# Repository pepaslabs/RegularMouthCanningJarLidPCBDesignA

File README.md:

# RegularMouthCanningJarLidPCBDesignA

A PCB which acts as a lid for a regular mouth canning jar.

# Status

This is still an untested work-in-progress.

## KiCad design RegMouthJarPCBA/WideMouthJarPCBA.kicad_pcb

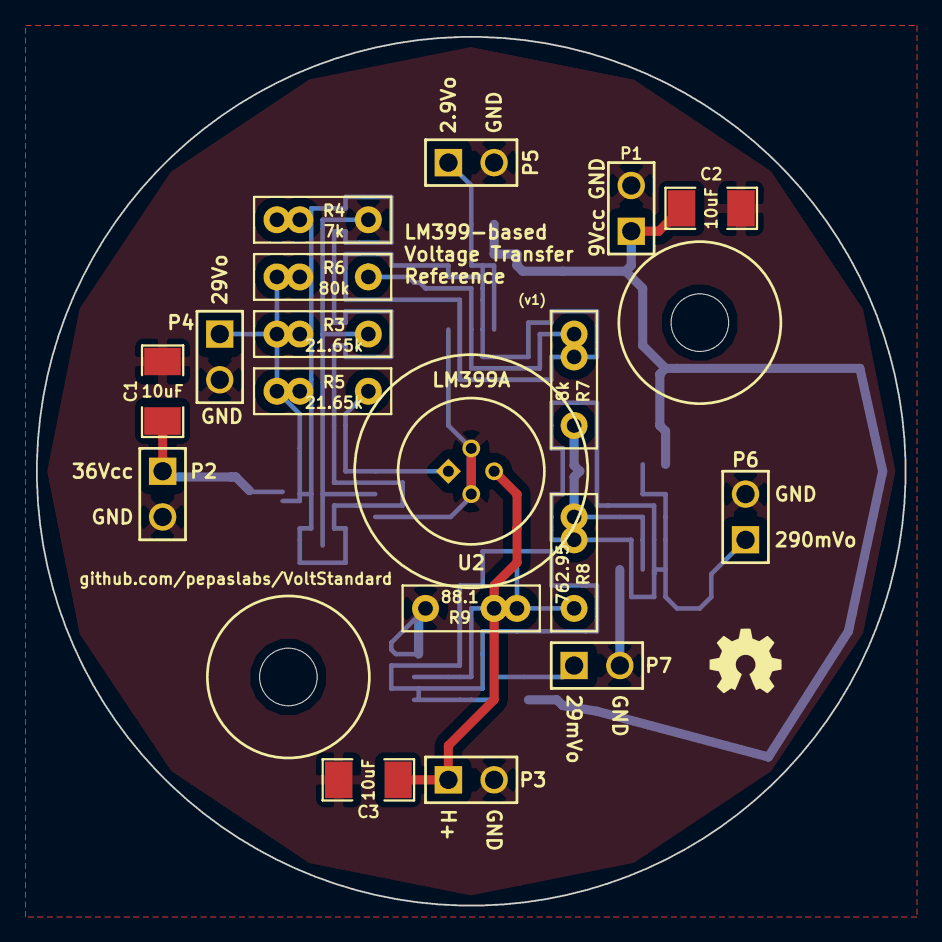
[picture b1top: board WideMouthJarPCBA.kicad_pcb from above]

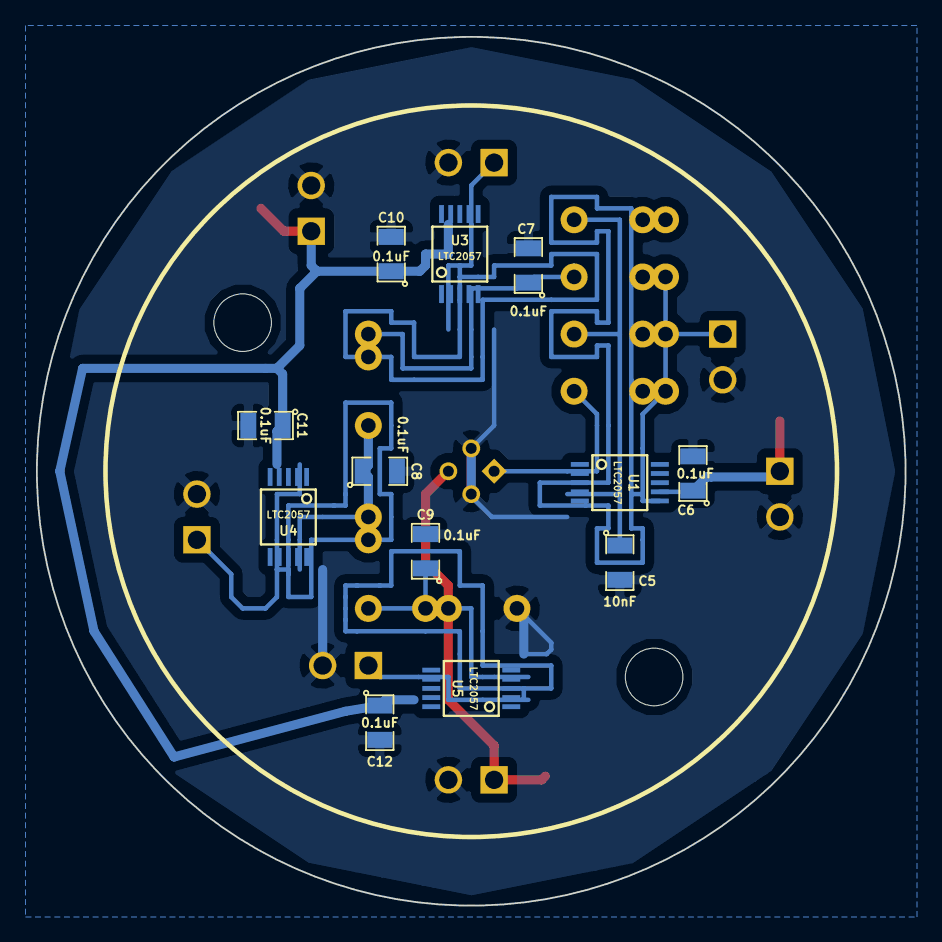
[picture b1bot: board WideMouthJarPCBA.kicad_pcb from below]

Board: 2 copper layers, 48.3 x 48.3 mm, 32 parts (12 on the bottom side), 13 nets.

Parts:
C1, C2, C3: 10uF; SM1206
C5: 10nF; SM0805
C6, C7, C8, C9, C10, C11, C12: 0.1uF; SM0805
H***: Val**; hole_M3
H***#2: Val**; hole_M3
P1, P2, P3, P4, P5, P6, P7: CONN_2; PIN_ARRAY_2X1
R3, R5: 21.65k; R_BOX
R4: 7k; R_BOX
R6: 80k; R_BOX
R7: 8k; R_BOX
R8: 762.95; R_BOX
R9: 88.1; R_BOX
U1, U3, U4, U5: LTC2057; MSOP10-0.5
U2: LM399A; TO-46-PLASTIC

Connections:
2.9Vo: P5.1, U3.2, U3.6
9V: C2.1, C10.1, C11.1, C12.1, P1.1, U3.7, U4.7, U5.7
29Vo: P4.1, R3.1, R5.1, R6.1, U1.6
29mVo: P7.1, U5.2, U5.6
36V: C1.1, C6.1, P2.1, U1.7
290mVo: P6.1, U4.2, U4.6
/2.9V: C7.1, R6.2, R7.1, U3.3
/29mV: C9.1, R8.2, R9.1, U5.3
/290mV: C8.1, R7.2, R8.1, U4.3
/Op-: C5.1, R3.2, R4.1, U1.3
/Vz: R5.2, U1.2, U2.1
GND: C1.2, C2.2, C3.2, C5.2, C6.2, C7.2, C8.2, C9.2, C10.2, C11.2, C12.2, P1.2, P2.2, P3.2, P4.2, P5.2, P6.2, P7.2, R4.2, R9.2, U1.4, U2.2, U2.4, U3.4, U4.4, U5.4
H+: C3.1, P3.1, U2.3

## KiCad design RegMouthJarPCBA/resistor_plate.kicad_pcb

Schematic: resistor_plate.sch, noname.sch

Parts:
H1, H2: HOLE
P1: CONN_4
R1, R2, R3, R4: R

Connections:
unnamed: R1.1, R4.1
unnamed: P1.3, P1.4, R2.2, R3.2, R4.2
unnamed: P1.1, P1.2, R1.2, R2.1, R3.1

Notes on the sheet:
Pinout: 1: Sense+ 2: Force+ 3: Force- 4: Sense-

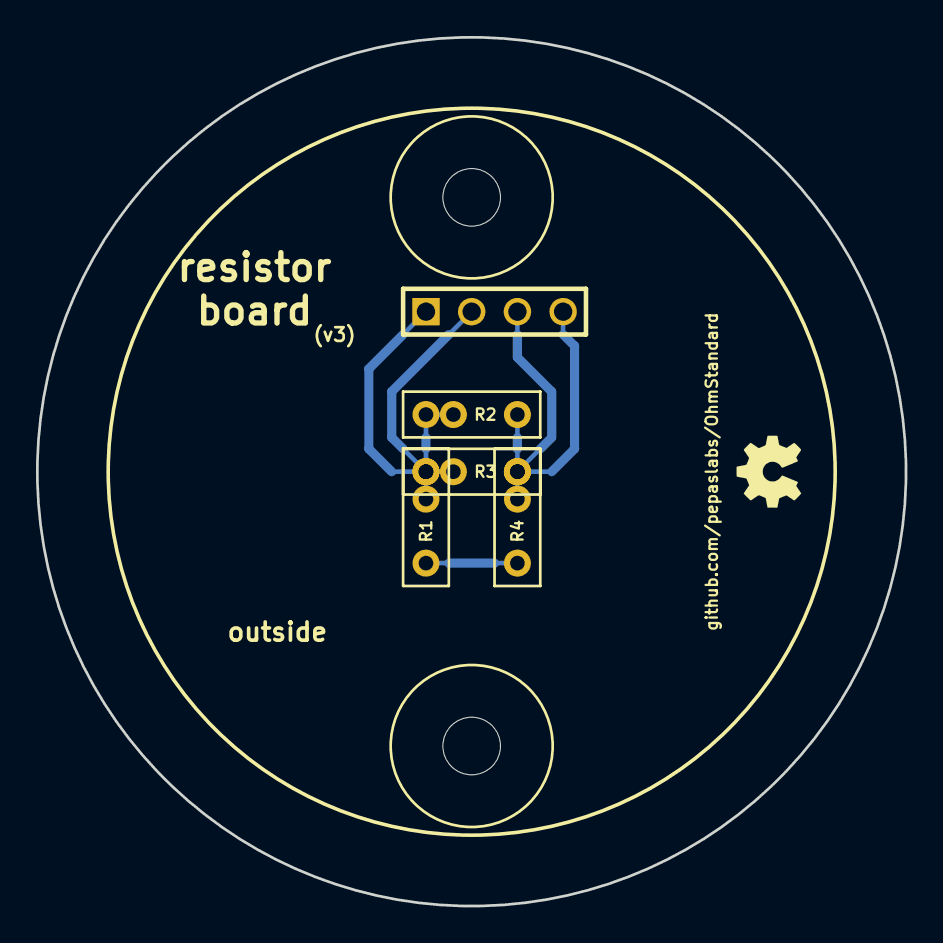
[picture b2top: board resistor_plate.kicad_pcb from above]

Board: 2 copper layers, 48.3 x 48.3 mm, 7 parts (0 on the bottom side), 3 nets.

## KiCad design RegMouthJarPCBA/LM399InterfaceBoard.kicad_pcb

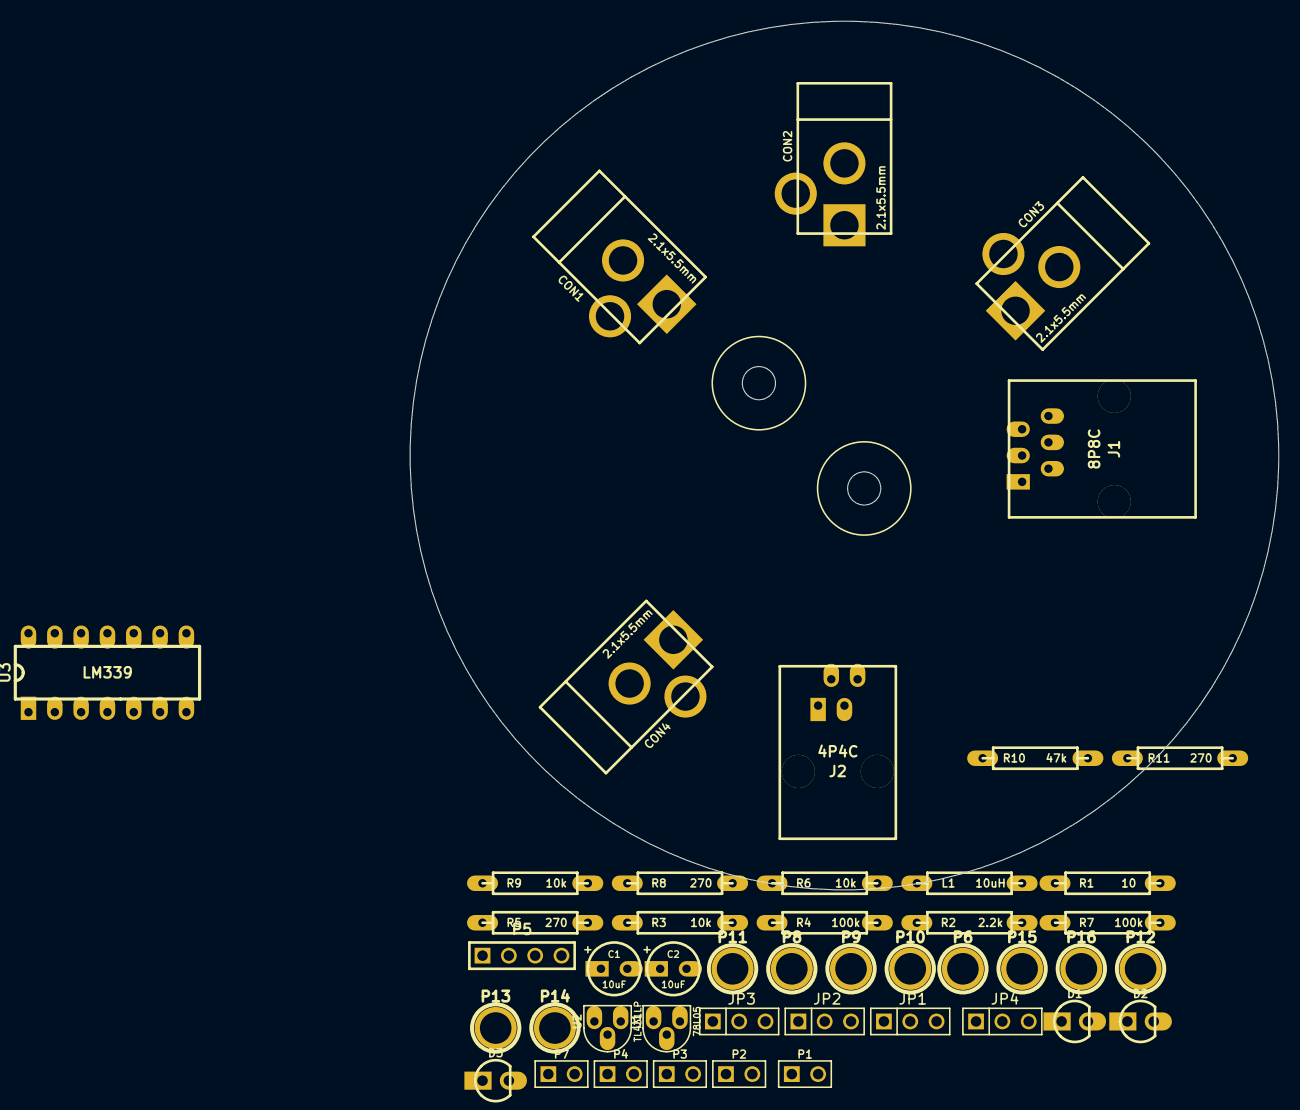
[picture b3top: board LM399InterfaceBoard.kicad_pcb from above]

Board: 2 copper layers, 83.8 x 83.8 mm, 48 parts (0 on the bottom side), 29 nets, no tracks yet.

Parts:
C1, C2: 10uF; ELCAP_10_20_V_059Bo
CON1, CON2, CON3, CON4: BARREL_JACK; BARREL_JACK_21x55
D1, D2, D3: LED; LED_3MM
H1, H2: HOLE; hole_M3_NPTH
J1: 8P8C; A-2004-1-4-LP-N-R_059Bo
J2: 4P4C; A-2014-3-4-N-T-R_059Bo
JP1, JP2, JP3, JP4: JUMPER3; PIN_ARRAY_3X1
L1: 10uH; R_AXIAL_0W25_059C
P1, P2, P3, P4, P7: CONN_2; PIN_ARRAY_2X1
P5: CONN_4; PIN_ARRAY_4x1
P6, P8, P9, P10, P11, P12, P13, P14, P15, P16: TST; 1pin
R1: 10; R_AXIAL_0W25_059C
R2: 2.2k; R_AXIAL_0W25_059C
R3, R6, R9: 10k; R_AXIAL_0W25_059C
R4, R7: 100k; R_AXIAL_0W25_059C
R5, R8, R11: 270; R_AXIAL_0W25_059C
R10: 47k; R_AXIAL_0W25_059C
U1: 78L05; TO-92_U_059Bo
U2: TL431LP; TO-92_U_059Bo
U3: LM339; DIP14

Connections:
2.5V: R2.2, U2.1, U2.2, U3.5, U3.7, U3.11
2.9V: J1.3, P2.1
5V: C2.1, R2.1, R5.1, R8.1, R11.1, U1.3, U3.3
9V: CON2.1, JP1.2, P9.1, R6.1
29V: J1.1, P1.1
36V: CON1.1, JP1.1, JP2.1, P8.1, R3.1
290mV: J1.5, P3.1
GND: C1.2, C2.2, CON1.2, CON1.3, CON2.2, CON2.3, CON3.2, CON3.3, JP4.2, P6.1, R4.2, R7.2, R10.2, U1.2, U2.3, U3.12
H+: CON3.1, JP2.2, JP3.1, P10.1, R1.1, R9.1
unnamed: D2.2, U3.1
unnamed: D2.1, R8.2
unnamed: L1.1, R1.2
unnamed: D1.1, R5.2
unnamed: D1.2, U3.2
unnamed: C1.1, L1.2, U1.1
unnamed: D3.1, R11.2
unnamed: U3.8, U3.9, U3.14
unnamed: D3.2, U3.13
unnamed: J2.1, P5.1
unnamed: J2.4, P5.4
unnamed: J2.3, P5.3
unnamed: J2.2, P5.2
unnamed: J1.4, P2.2
unnamed: J1.2, P1.2
unnamed: J1.6, P3.2
unnamed: P7.2, P16.1
unnamed: P7.1, P15.1
Oven+: CON4.1, JP3.2
Oven-: CON4.2, CON4.3, JP4.1

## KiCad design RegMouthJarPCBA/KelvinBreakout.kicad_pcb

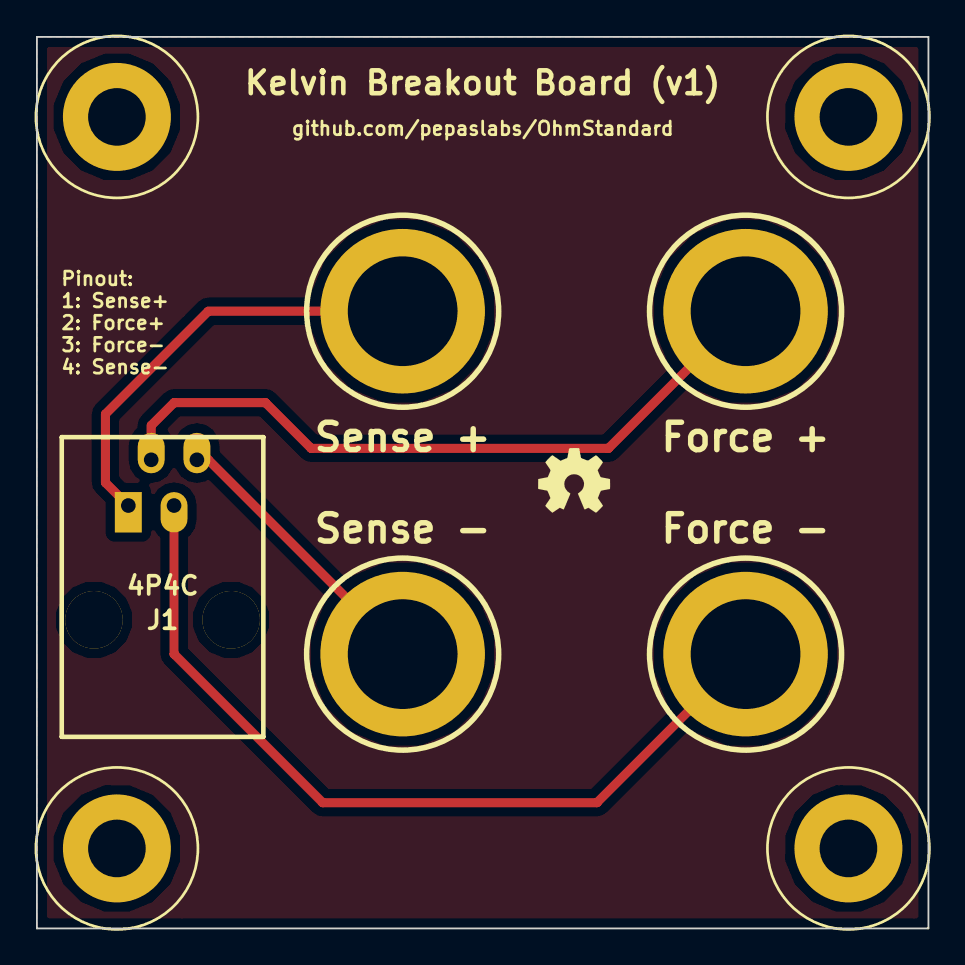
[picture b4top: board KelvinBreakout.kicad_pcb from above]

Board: 2 copper layers, 49.5 x 49.5 mm, 9 parts (0 on the bottom side), 4 nets.

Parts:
H1, H2, H3, H4: HOLE; hole_M3
J1: 4P4C; A-2014-3-4-N-T-R_059Bo
P1: Sense +; Banana_A
P2: Force +; Banana_A
P3: Force -; Banana_A
P4: Sense -; Banana_A

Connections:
unnamed: J1.2, P2.1
unnamed: J1.4, P4.1
unnamed: J1.3, P3.1
unnamed: J1.1, P1.1

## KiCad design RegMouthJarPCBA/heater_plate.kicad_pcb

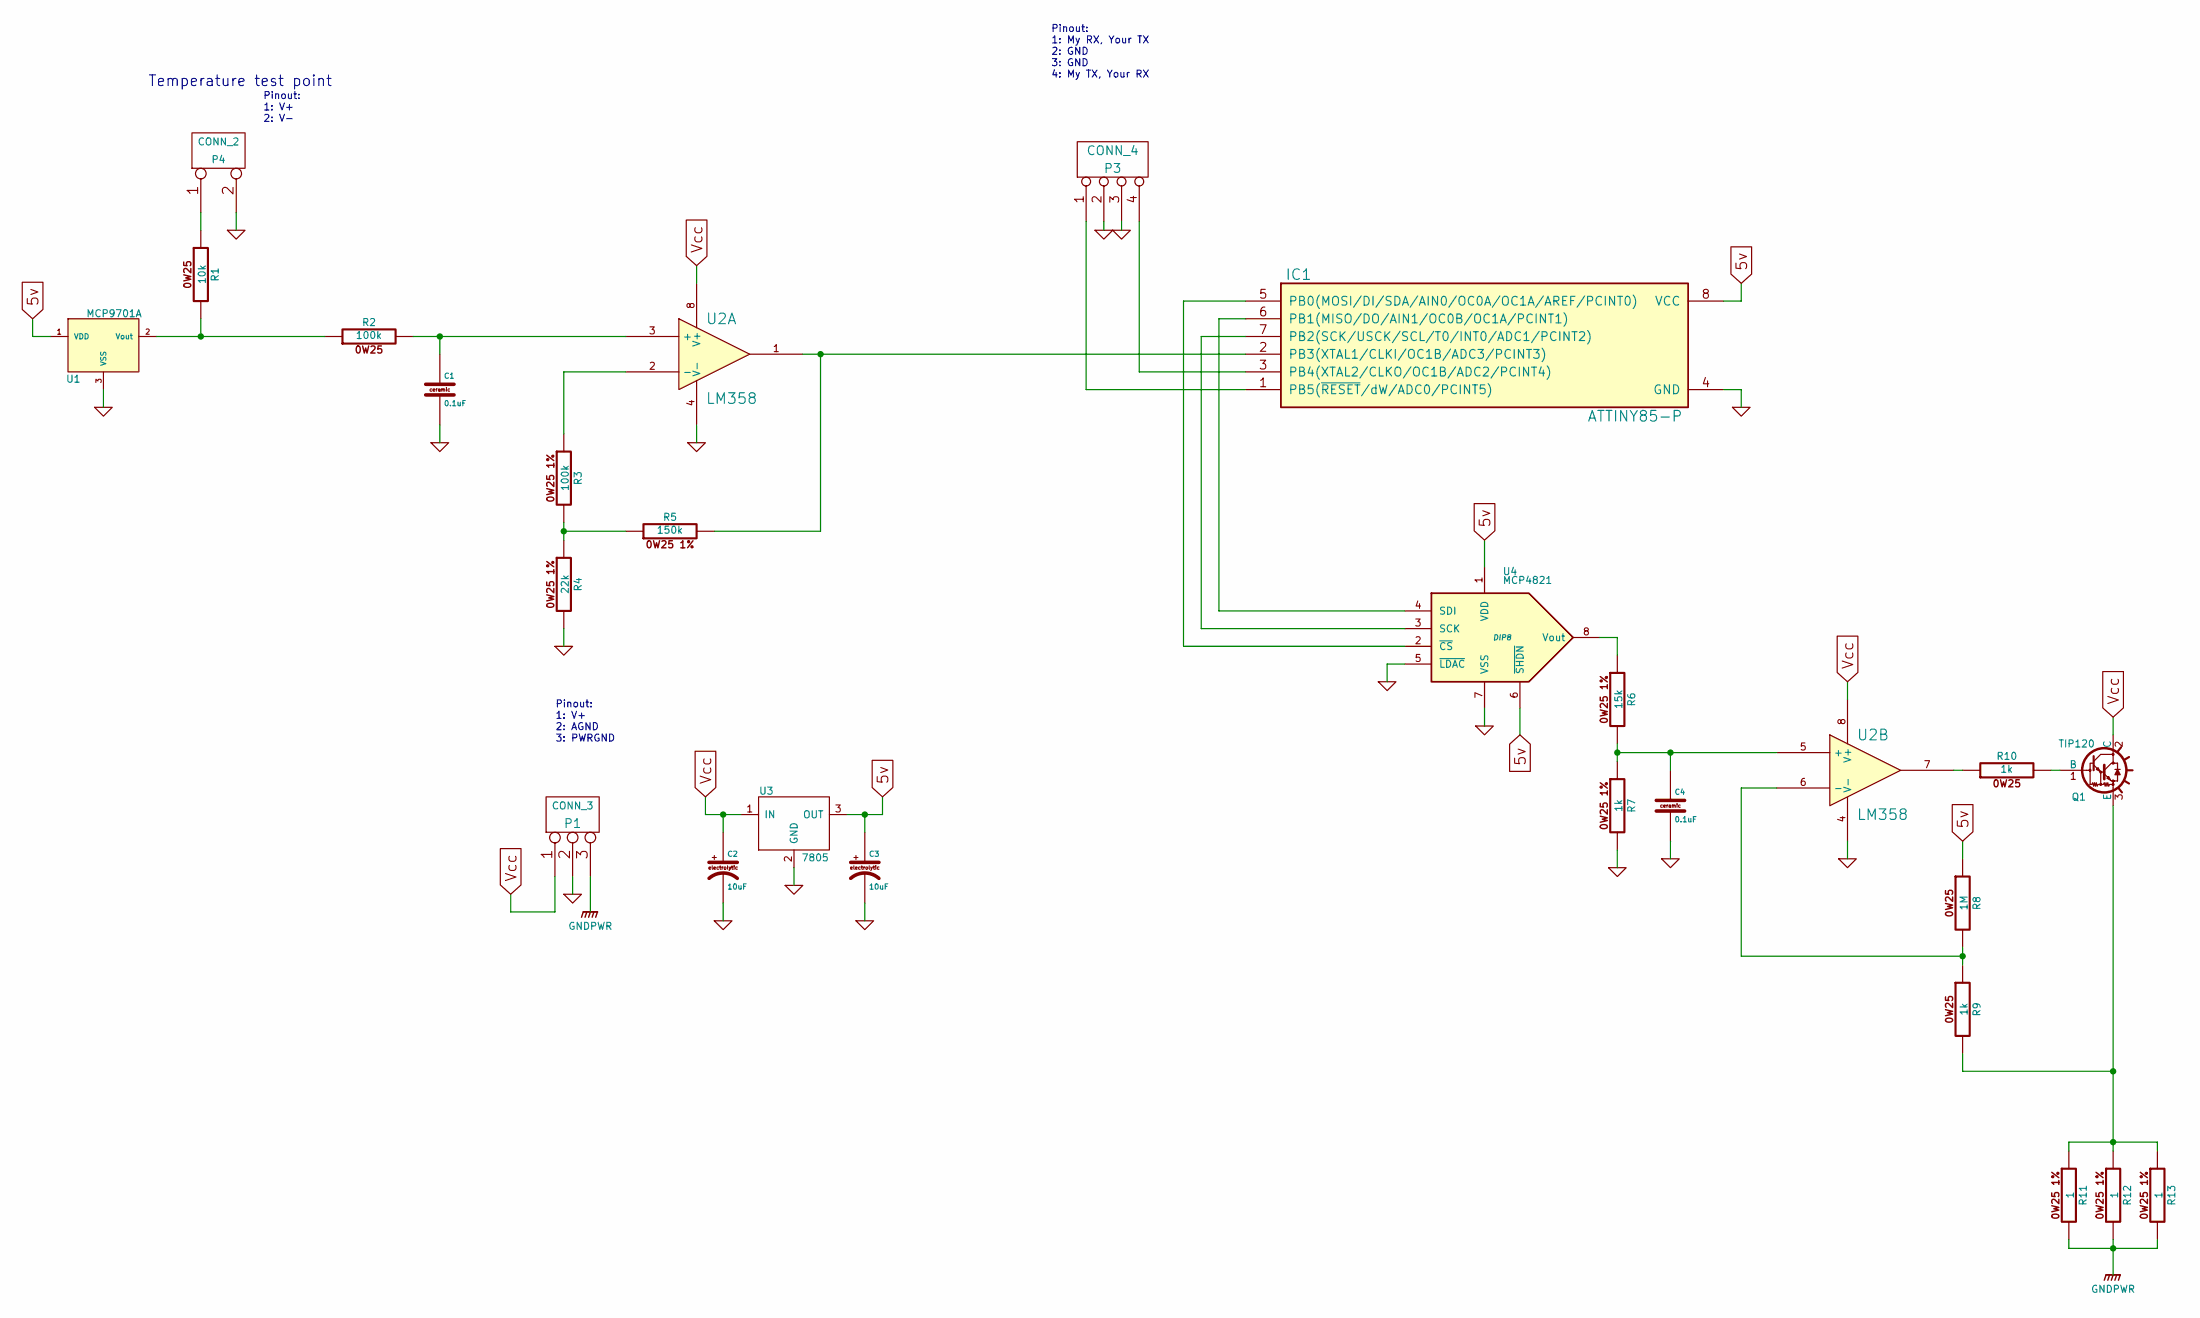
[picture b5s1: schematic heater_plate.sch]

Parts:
C1, C4: 0.1uF
C2, C3: 10uF
IC1: ATTINY85-P; DIP8
P1: CONN_3
P3: CONN_4
P4: CONN_2
Q1: TIP120; TO220
R1: 10k
R2, R3: 100k
R4: 22k
R5: 150k
R6: 15k
R7, R9, R10: 1k
R8: 1M
R11, R12, R13: 1
U1: MCP9701A
U2: LM358
U3: 7805
U4: MCP4821; DIP8

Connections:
5v: C3.1, IC1.8 (VCC), R8.1, U1.1 (VDD), U3.3 (OUT), U4.1 (VDD), U4.6 (~SHDN~)
GND: C1.2, C2.2, C3.2, C4.2, IC1.4 (GND), P1.2 (PM), P3.2, P3.3, P4.2 (PM), R4.2, R7.2, U1.3 (VSS), U2.4 (V-), U3.2 (GND), U4.5 (~LDAC~), U4.7 (VSS)
GNDPWR: P1.3, R11.2, R12.2, R13.2
unnamed: C1.1, R2.2, U2.3 (+)
unnamed: R3.1, U2.2 (-)
unnamed: R3.2, R4.1, R5.1
unnamed: IC1.2 (PB3(XTAL1/CLKI/OC1B/ADC3/PCINT3)), R5.2, U2.1
unnamed: IC1.7 (PB2(SCK/USCK/SCL/T0/INT0/ADC1/PCINT2)), U4.3 (SCK)
unnamed: R1.2, R2.1, U1.2 (Vout)
unnamed: P4.1, R1.1
unnamed: C4.1, R6.2, R7.1, U2.5 (+)
unnamed: IC1.5 (PB0(MOSI/DI/SDA/AIN0/OC0A/OC1A/AREF/PCI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), U4.2 (~CS~)
unnamed: IC1.6 (PB1(MISO/DO/AIN1/OC0B/OC1A/PCINT1)), U4.4 (SDI)
unnamed: IC1.3 (PB4(XTAL2/CLKO/OC1B/ADC2/PCINT4)), P3.4
unnamed: IC1.1 (PB5(~RESET~/dW/ADC0/PCINT5)), P3.1
unnamed: R10.1, U2.7
unnamed: Q1.1 (B), R10.2
unnamed: R8.2, R9.1, U2.6 (-)
unnamed: R6.1, U4.8 (Vout)
unnamed: Q1.3 (E), R9.2, R11.1, R12.1, R13.1
Vcc: C2.1, P1.1, Q1.2 (C), U2.8 (V+), U3.1 (IN)

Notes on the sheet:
Pinout: 1: My RX, Your TX 2: GND 3: GND 4: My TX, Your RX
Pinout: 1: V+ 2: AGND 3: PWRGND
Temperature test point
Pinout: 1: V+ 2: V-

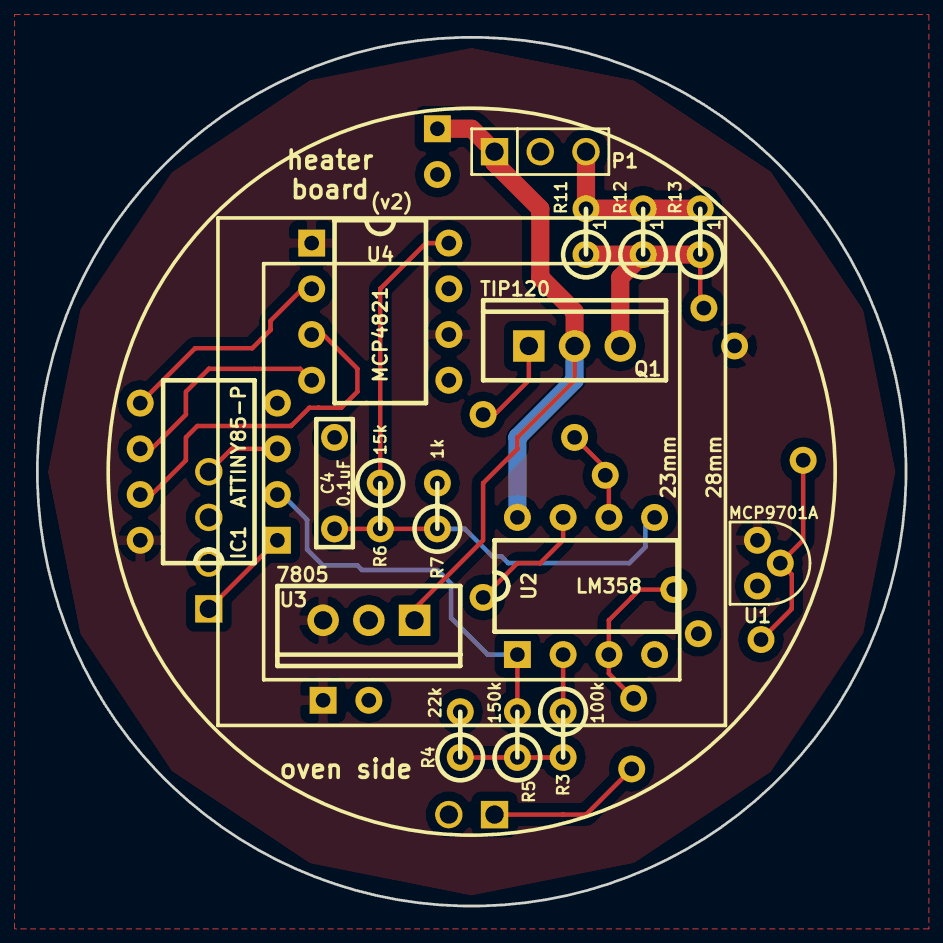
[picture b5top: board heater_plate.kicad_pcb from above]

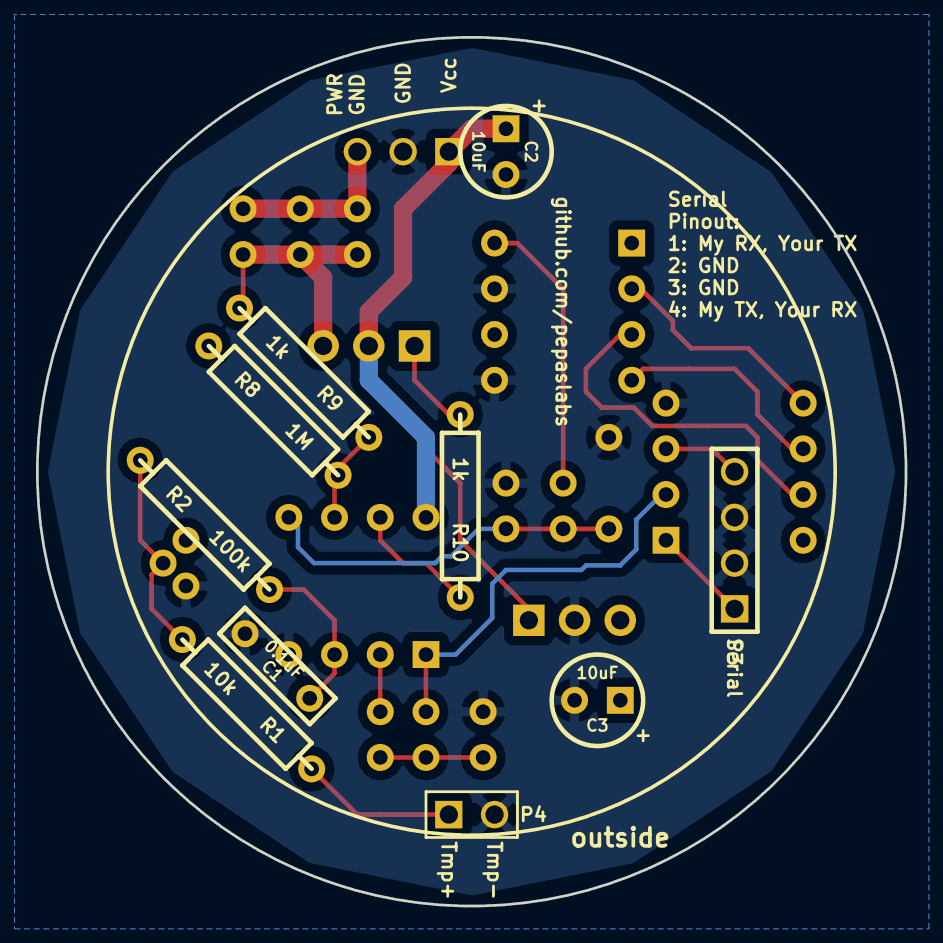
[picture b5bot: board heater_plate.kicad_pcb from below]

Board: 2 copper layers, 48.3 x 48.3 mm, 26 parts (10 on the bottom side), 21 nets.

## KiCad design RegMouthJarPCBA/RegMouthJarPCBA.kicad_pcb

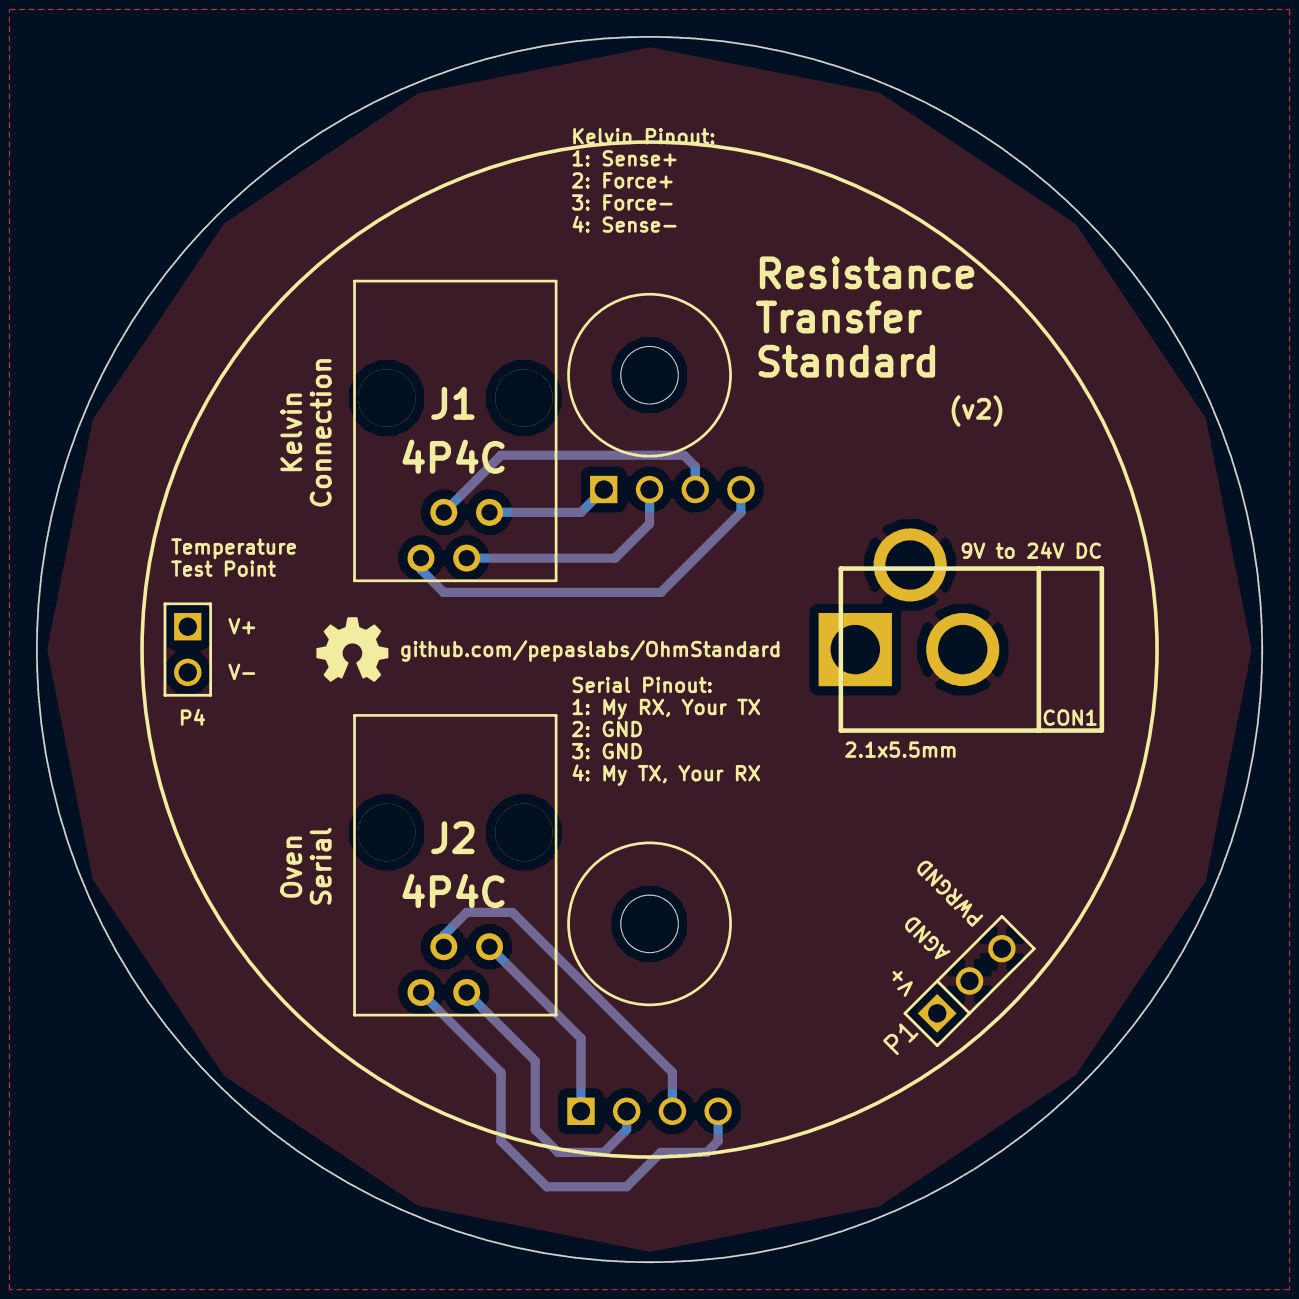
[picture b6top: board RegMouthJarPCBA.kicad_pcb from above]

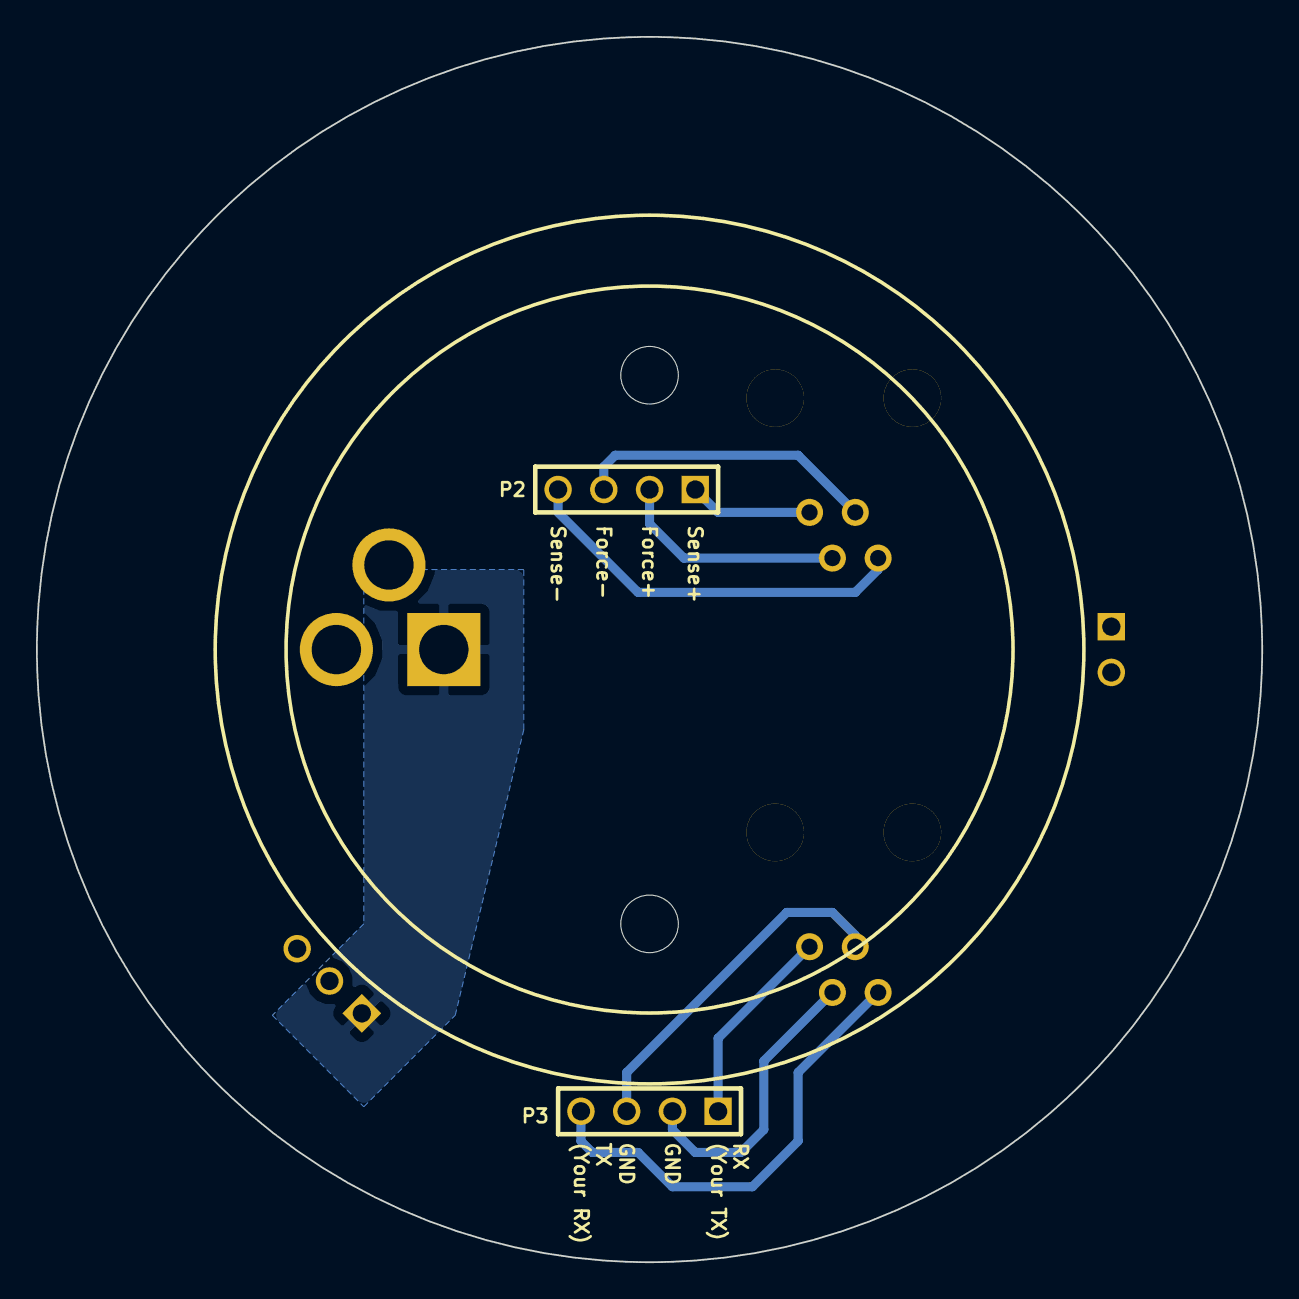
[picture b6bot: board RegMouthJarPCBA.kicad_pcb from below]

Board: 2 copper layers, 68.1 x 68.1 mm, 9 parts (2 on the bottom side), 10 nets.

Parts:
CON1: BARREL_JACK; BARREL_JACK_21x55
H1, H2: HOLE; hole_M3
J1, J2: 4P4C; A-2014-3-4-N-T-R
P1: CONN_3; PIN_ARRAY_3X1
P2, P3: CONN_4; PIN_ARRAY_4x1
P4: CONN_2; PIN_ARRAY_2X1

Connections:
GND: CON1.2, CON1.3, P1.2, P1.3
unnamed: J1.4, P2.4
unnamed: CON1.1, P1.1
unnamed: J2.1, P3.1
unnamed: J2.2, P3.2
unnamed: J2.3, P3.3
unnamed: J2.4, P3.4
unnamed: J1.1, P2.1
unnamed: J1.2, P2.2
unnamed: J1.3, P2.3

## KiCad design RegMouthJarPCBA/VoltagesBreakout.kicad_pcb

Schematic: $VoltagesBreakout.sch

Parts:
H1, H2, H3, H4: HOLE
J1: 8P8C
P1, P2, P3, P4, P5, P6, P7, P8: CONN_1

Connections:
unnamed: J1.6, P6.1
unnamed: J1.2, P2.1
unnamed: J1.3, P3.1
unnamed: J1.4, P4.1
unnamed: J1.5, P5.1
unnamed: J1.7, P7.1
unnamed: J1.8, P8.1
unnamed: J1.1, P1.1

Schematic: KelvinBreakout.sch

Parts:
H1, H2, H3, H4: HOLE
J1: 4P4C
P1, P2, P3, P4: CONN_1

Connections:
unnamed: J1.2, P2.1
unnamed: J1.3, P3.1
unnamed: J1.4, P4.1
unnamed: J1.1, P1.1

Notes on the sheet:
Pinout: 1: Sense+ 2: Force+ 3: Force- 4: Sense-

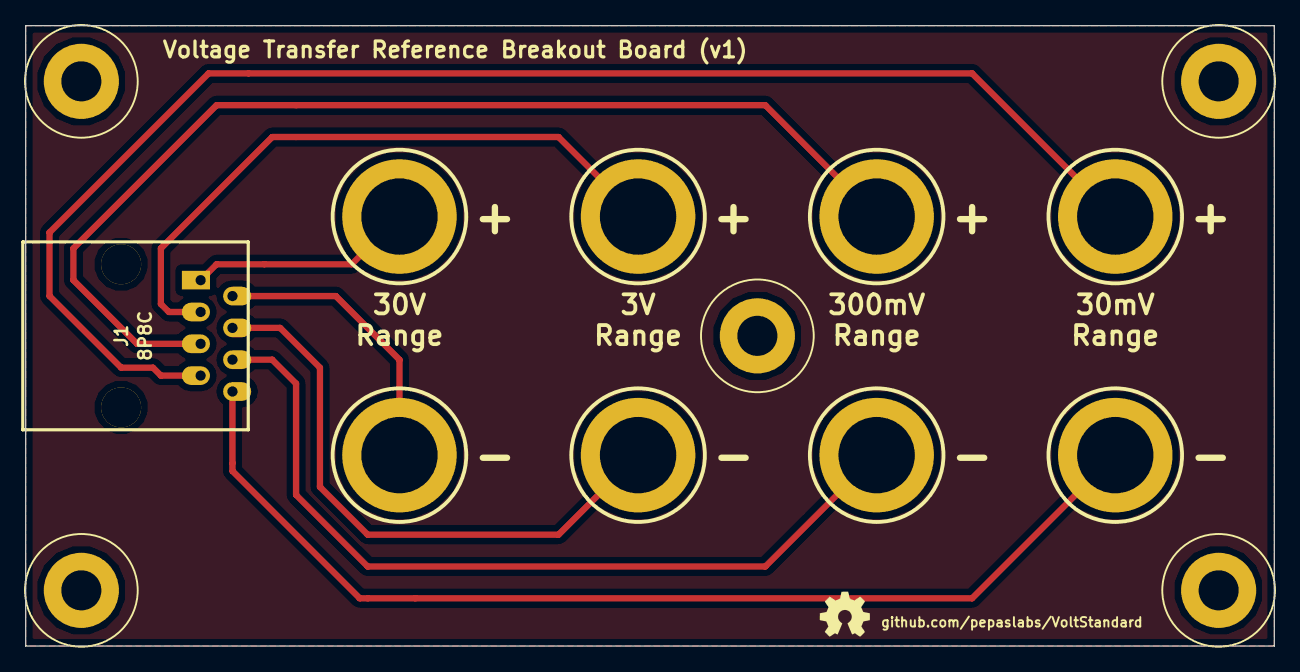
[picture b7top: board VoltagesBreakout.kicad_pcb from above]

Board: 2 copper layers, 99.7 x 49.5 mm, 14 parts (0 on the bottom side), 8 nets.

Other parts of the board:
H***: Val**; hole_M3

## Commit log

2014-06-06 initial rough design of jar lid PCB.
2014-06-06 adding temperature test point
2014-06-06 tweaking board layout.
2014-06-06 finalizing v1 board design and creating gerbers.
2014-06-06 forgot to save changes in pcb file.
2014-06-26 bulk update. starting tweaks for v2.
2014-06-27 adding first pass at design of LM399 voltage standard.
2014-06-29 first revision of the LM399 board.
2014-06-29 implemented guard traces for LM399 reference board. producing pcb's as v1.
2014-06-29 fixing a bug in the gaurd trace solder mask.
2014-06-29 revising github url
2014-06-30 updating connectors library. starting on banana jack breakout boards.
2014-06-30 adding 8P8C connector.
2014-06-30 finished voltage breakout board v1.
2014-06-30 adding kelvin breakout board (v1)
2014-07-01 updating voltage breakout board to fit within 10cm x 5cm for seeedstudio.
2014-07-01 updating resistor board to v2.
2014-07-02 updating LM399 interface board schematic
2014-07-04 LM399 board WIP.
2014-07-09 updating resistor board to v3.
2014-07-09 cleanup
2014-07-15 switching to combined 0.15" / 0.2" spaced resistor footprints.
2014-07-15 substituting 10-pin LTC2057's.
2017-04-22 updating readme
